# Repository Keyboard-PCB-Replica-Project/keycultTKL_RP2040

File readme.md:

키컬트(Keycult) TKL 레플리카 PCB입니다. 

LED는 따로 부착해두지 않았습니다.

KT-0805W LED를 구입해서 LED 자리에 납땜해주시면 됩니다. 타오바오나 알리에서 같이 주문해주시면 되며,

납땜 난이도는 스위치보다도 못한 수준입니다.

물론 돈이 더 들어도 괜찮다면, LED까지 부착이 된 채로 배송 오는 옵션을 구현해두겠습니다.

이 기판은 ISO를 지원하지 않습니다!

추후에 추가될 수도 있습니다.

추가 필요 부품 : KT-0805W LED

작동 확인 여부 : 아직 확인되지 않음

----------------------------------------------------------

This is a replica PCB for the Keycult TKL.

LEDs are not included.

You can buy KT-0805W LEDs and solder them yourself.

They’re easy to find on Taobao or AliExpress, and the soldering is even easier than doing switches.

If you're okay with spending a bit more, I might offer a version with the LEDs pre-installed later on.

This PCB does not support ISO layout.

It might be added in a future version.

Extra parts needed: KT-0805W LEDs

Tested and working: Not verified yet

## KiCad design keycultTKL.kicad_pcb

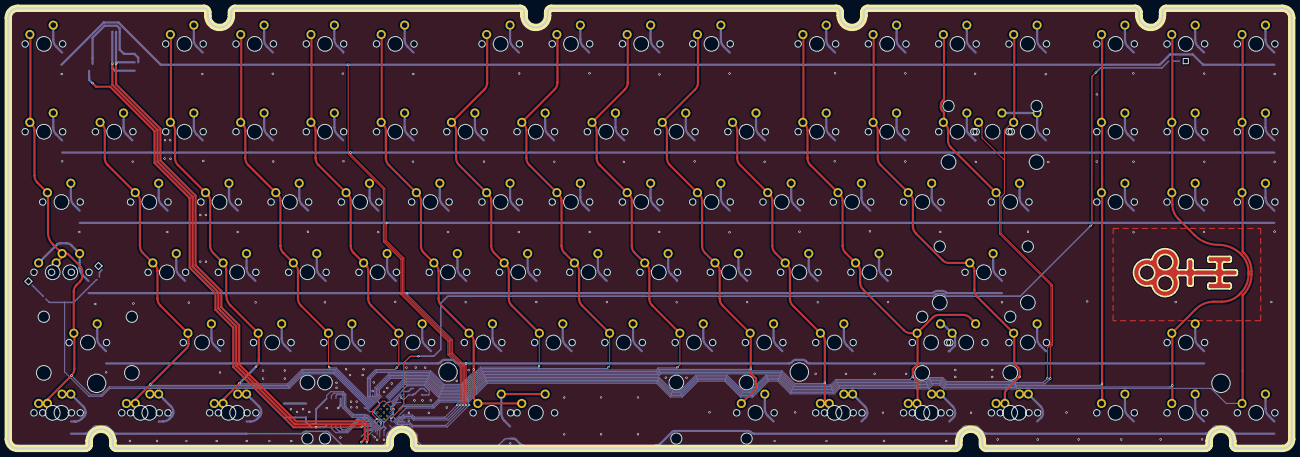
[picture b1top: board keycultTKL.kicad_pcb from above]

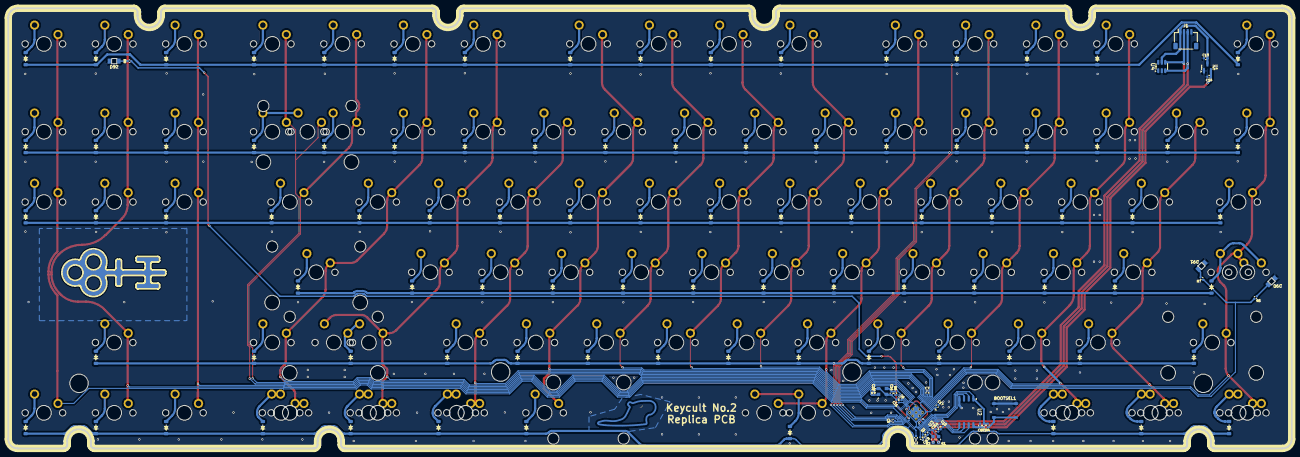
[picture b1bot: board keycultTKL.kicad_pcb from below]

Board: 2 copper layers, 347.9 x 119.3 mm, 213 parts (124 on the bottom side), 136 nets.

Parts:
BOOTSEL1: SW_Push; SW_Push_1P1T_XKB_TS-1187A
C1, C2, C3, C4, C5, C6, C7, C8, C10, C11, C17: 100n; C_0402_1005Metric
C9, C12, C13, C14: 1u; C_0402_1005Metric
C15, C16: 15p; C_0402_1005Metric
D1, D2, D3, D4, D5, D6, D7, D8, D9, D10, D11, D12, D13, D14, D15, D16, D17, D18, D19, D20, D21, D22, D23, D24, D25, D26, D27, D28, D29, D30, D31, D32, D33, D34, D35, D36, D37, D38, D39, D40, D41, D42, D43, D44, D45, D46, D47, D48, D49, D50, D51, D52, D53, D54, D55, D56, D57, D58, D59, D60, D61, D62, D63, D64, D65, D66, D67, D68, D69, D70, D71, D72, D73, D74, D75, D76, D77, D78, D79, D80, D81, D82, D83, D84, D85, D86, D87, D88, D89: D_Small; Diode_SOD-123_noref2
D90, D91, D92: LED; KT-0805W
J1: Conn_01x04; JST_SH_SM04B-SRSS-TB_1x04-1MP_P1.00mm_Horizontal
MX1, MX2, MX3, MX4, MX5, MX6, MX7, MX8, MX9, MX10, MX11, MX12, MX13, MX14, MX15, MX16, MX17, MX18, MX19, MX20, MX21, MX22, MX23, MX24, MX25, MX26, MX27, MX28, MX29, MX30, MX31, MX32, MX33, MX34, MX35, MX36, MX37, MX38, MX39, MX40, MX41, MX42, MX43, MX44, MX45, MX46, MX47, MX48, MX49, MX50, MX51, MX52, MX53, MX54, MX55, MX56, MX57, MX58, MX59, MX60, MX61, MX62, MX63, MX64, MX65, MX66, MX67, MX68, MX69, MX70, MX71, MX72, MX73, MX74, MX75, MX76, MX77, MX78, MX79, MX80, MX81, MX82, MX83, MX84, MX85, MX86, MX87, MX88, MX89: MX_SW_solder; MX_PCB_1.00u_NoSilkscreen3
R1, R2: 27.4; C_0603_1608Metric
R3: 10k; C_0402_1005Metric
R4: 1k; C_0402_1005Metric
R5, R7, R8: 300R; C_0402_1005Metric
R6: 1K; C_0402_1005Metric
U1: XC6206PxxxMR; SOT-23
U2: W25Q128JVS; SOIC-8_5.23x5.23mm_P1.27mm
U3: RP2040; RP2040-QFN-56
U4: SRV05-4; SOT-23-6
Y1: ABM8-272-T3; Oscillator_SMD_EuroQuartz_XO32-4Pin_3.2x2.5mm

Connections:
+1V1: C10.1, C11.1, C12.1, U3.23 (DVDD), U3.45 (VREG_VOUT), U3.50 (DVDD)
+3V3: C1.2, C2.2, C3.2, C4.2, C5.2, C6.2, C7.2, C8.1, C9.1, C14.1, C17.2, R3.1, U1.2 (VO), U2.8 (VCC), U3.1 (IOVDD), U3.10 (IOVDD), U3.22 (IOVDD), U3.33 (IOVDD), U3.42 (IOVDD), U3.43 (ADC_AVDD), U3.44 (VREG_IN), U3.48 (USB_VDD), U3.49 (IOVDD)
/QSPI_SCLK: U2.6 (CLK), U3.52 (QSPI_SCLK)
/QSPI_SD0: U2.5 (DI(IO0)), U3.53 (QSPI_SD0)
/QSPI_SD1: U2.2 (DO(IO1)), U3.55 (QSPI_SD1)
/QSPI_SD2: U2.3 (IO2), U3.54 (QSPI_SD2)
/QSPI_SD3: U2.7 (IO3), U3.51 (QSPI_SD3)
/QSPI_SS: R3.2, R4.2, U2.1 (~CS), U3.56 (QSPI_SS)
Col0: MX1.1, MX17.1, MX35.1, MX52.1, MX65.1, MX79.1, U3.3 (GPIO1)
Col1: MX18.1, MX36.1, MX53.1, MX66.1, MX80.1, U3.4 (GPIO2)
Col2: MX2.1, MX19.1, MX37.1, MX54.1, MX67.1, MX81.1, U3.5 (GPIO3)
Col3: MX3.1, MX20.1, MX38.1, MX55.1, MX68.1, U3.6 (GPIO4)
Col4: MX4.1, MX21.1, MX39.1, MX56.1, MX69.1, U3.7 (GPIO5)
Col5: MX5.1, MX22.1, MX40.1, MX57.1, MX70.1, MX82.1, U3.8 (GPIO6)
Col6: MX6.1, MX23.1, MX41.1, MX58.1, MX71.1, U3.9 (GPIO7)
Col7: MX7.1, MX24.1, MX42.1, MX59.1, MX72.1, U3.11 (GPIO8)
Col8: MX8.1, MX25.1, MX43.1, MX60.1, MX73.1, U3.12 (GPIO9)
Col9: MX9.1, MX26.1, MX44.1, MX61.1, MX74.1, MX83.1, U3.13 (GPIO10)
Col10: MX27.1, MX45.1, MX62.1, MX75.1, MX84.1, U3.14 (GPIO11)
Col11: MX10.1, MX28.1, MX46.1, MX63.1, MX76.1, MX85.1, U3.15 (GPIO12)
Col12: MX11.1, MX29.1, MX47.1, MX64.1, MX77.1, MX86.1, U3.16 (GPIO13)
Col13: MX12.1, MX30.1, MX48.1, U3.17 (GPIO14)
Col14: MX13.1, MX31.1, U3.18 (GPIO15)
Col15: MX14.1, MX32.1, MX49.1, MX87.1, U3.27 (GPIO16)
Col16: MX15.1, MX33.1, MX50.1, MX78.1, MX88.1, U3.28 (GPIO17)
Col17: MX16.1, MX34.1, MX51.1, MX89.1, U3.29 (GPIO18)
DM: J1.2, R2.2, U4.4 (IO3)
DP: J1.3, R1.1, U4.3 (IO2)
GND: BOOTSEL1.1, C1.1, C2.1, C3.1, C4.1, C5.1, C6.1, C7.1, C8.2, C9.2, C10.2, C11.2, C12.2, C13.2, C14.2, C15.1, C16.1, C17.1, D90.1 (K), D91.1 (K), D92.1 (K), J1.4, U1.1 (GND), U2.4 (GND), U3.19 (TESTEN), U3.57 (GND), U4.2 (VN), Y1.2, Y1.4
unnamed: BOOTSEL1.2, R4.1
unnamed: C16.2, R6.1, Y1.3
unnamed: D1.2 (A), MX1.2
unnamed: D2.2 (A), MX2.2
unnamed: D3.2 (A), MX3.2
unnamed: D4.2 (A), MX4.2
unnamed: D5.2 (A), MX5.2
unnamed: D6.2 (A), MX6.2
unnamed: D7.2 (A), MX7.2
unnamed: D8.2 (A), MX8.2
unnamed: D9.2 (A), MX9.2
unnamed: D10.2 (A), MX10.2
unnamed: D11.2 (A), MX11.2
unnamed: D12.2 (A), MX12.2
unnamed: D13.2 (A), MX13.2
unnamed: D14.2 (A), MX14.2
unnamed: D15.2 (A), MX15.2
unnamed: D16.2 (A), MX16.2
unnamed: D17.2 (A), MX17.2
unnamed: D18.2 (A), MX18.2
unnamed: D19.2 (A), MX19.2
unnamed: D20.2 (A), MX20.2
unnamed: D21.2 (A), MX21.2
unnamed: D22.2 (A), MX22.2
unnamed: D23.2 (A), MX23.2
unnamed: D24.2 (A), MX24.2
unnamed: D25.2 (A), MX25.2
unnamed: D26.2 (A), MX26.2
unnamed: D27.2 (A), MX27.2
unnamed: D28.2 (A), MX28.2
unnamed: D29.2 (A), MX29.2
unnamed: D30.2 (A), MX30.2
unnamed: D31.2 (A), MX31.2
unnamed: D32.2 (A), MX32.2
unnamed: D33.2 (A), MX33.2
unnamed: D34.2 (A), MX34.2
unnamed: D35.2 (A), MX35.2
unnamed: D36.2 (A), MX36.2
unnamed: D37.2 (A), MX37.2
unnamed: D38.2 (A), MX38.2
unnamed: D39.2 (A), MX39.2
unnamed: D40.2 (A), MX40.2
unnamed: D41.2 (A), MX41.2
unnamed: D42.2 (A), MX42.2
unnamed: D43.2 (A), MX43.2
unnamed: D44.2 (A), MX44.2
unnamed: D45.2 (A), MX45.2
unnamed: D46.2 (A), MX46.2
unnamed: D47.2 (A), MX47.2
unnamed: D48.2 (A), MX48.2
unnamed: D49.2 (A), MX49.2
unnamed: D50.2 (A), MX50.2
unnamed: D51.2 (A), MX51.2
unnamed: D52.2 (A), MX52.2
unnamed: D53.2 (A), MX53.2
unnamed: D54.2 (A), MX54.2
unnamed: D55.2 (A), MX55.2
unnamed: D56.2 (A), MX56.2
unnamed: D57.2 (A), MX57.2
unnamed: D58.2 (A), MX58.2
unnamed: D59.2 (A), MX59.2
unnamed: D60.2 (A), MX60.2
unnamed: D61.2 (A), MX61.2
unnamed: D62.2 (A), MX62.2
unnamed: D63.2 (A), MX63.2
unnamed: D64.2 (A), MX64.2
unnamed: D65.2 (A), MX65.2
unnamed: D66.2 (A), MX66.2
unnamed: D67.2 (A), MX67.2
unnamed: D68.2 (A), MX68.2
unnamed: D69.2 (A), MX69.2
unnamed: D70.2 (A), MX70.2
unnamed: D71.2 (A), MX71.2
unnamed: D72.2 (A), MX72.2
unnamed: D73.2 (A), MX73.2
unnamed: D74.2 (A), MX74.2
unnamed: D75.2 (A), MX75.2
unnamed: D76.2 (A), MX76.2
unnamed: D77.2 (A), MX77.2
unnamed: D78.2 (A), MX78.2
unnamed: D79.2 (A), MX79.2
unnamed: D80.2 (A), MX80.2
unnamed: D81.2 (A), MX81.2
unnamed: D82.2 (A), MX82.2
unnamed: D83.2 (A), MX83.2
unnamed: D84.2 (A), MX84.2
unnamed: D85.2 (A), MX85.2
unnamed: D86.2 (A), MX86.2
unnamed: D87.2 (A), MX87.2
unnamed: D88.2 (A), MX88.2
unnamed: D89.2 (A), MX89.2
unnamed: D90.2 (A), R5.1
unnamed: D91.2 (A), R7.1
unnamed: D92.2 (A), R8.1
unnamed: R5.2, R7.2, U3.2 (GPIO0)
unnamed: R8.2, U3.36 (GPIO24)
unnamed: R2.1, U3.46 (USB_DM)
unnamed: R1.2, U3.47 (USB_DP)
unnamed: C15.2, U3.20 (XIN), Y1.1
unnamed: R6.2, U3.21 (XOUT)
Row0: D1.1 (K), D2.1 (K), D3.1 (K), D4.1 (K), D5.1 (K), D6.1 (K), D7.1 (K), D8.1 (K), D9.1 (K), D10.1 (K), D11.1 (K), D12.1 (K), D13.1 (K), D14.1 (K), D15.1 (K), D16.1 (K), U3.30 (GPIO19)
Row1: D17.1 (K), D18.1 (K), D19.1 (K), D20.1 (K), D21.1 (K), D22.1 (K), D23.1 (K), D24.1 (K), D25.1 (K), D26.1 (K), D27.1 (K), D28.1 (K), D29.1 (K), D30.1 (K), D31.1 (K), D32.1 (K), D33.1 (K), D34.1 (K), U3.31 (GPIO20)
Row2: D35.1 (K), D36.1 (K), D37.1 (K), D38.1 (K), D39.1 (K), D40.1 (K), D41.1 (K), D42.1 (K), D43.1 (K), D44.1 (K), D45.1 (K), D46.1 (K), D47.1 (K), D48.1 (K), D49.1 (K), D50.1 (K), D51.1 (K), U3.32 (GPIO21)
Row3: D52.1 (K), D53.1 (K), D54.1 (K), D55.1 (K), D56.1 (K), D57.1 (K), D58.1 (K), D59.1 (K), D60.1 (K), D61.1 (K), D62.1 (K), D63.1 (K), D64.1 (K), U3.34 (GPIO22)
Row4: D65.1 (K), D66.1 (K), D67.1 (K), D68.1 (K), D69.1 (K), D70.1 (K), D71.1 (K), D72.1 (K), D73.1 (K), D74.1 (K), D75.1 (K), D76.1 (K), D77.1 (K), D78.1 (K), U3.35 (GPIO23)
Row5: D79.1 (K), D80.1 (K), D81.1 (K), D82.1 (K), D83.1 (K), D84.1 (K), D85.1 (K), D86.1 (K), D87.1 (K), D88.1 (K), D89.1 (K), U3.39 (GPIO27_ADC1)
VBUS: C13.1, J1.1, U1.3 (VI), U4.5 (VP)

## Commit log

2025-07-27 firmware update
